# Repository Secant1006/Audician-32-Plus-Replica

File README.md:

# Audician 32 Plus Replica

This is a reverse-engineered sound card based on [Labway A151-A00](https://theretroweb.com/expansioncards/s/labway-corporation-labsound-a00-ide-power-a), which is a Yamaha OPL3-SAx based sound card. The OPL3-SAx is a single solution sound chip which provides Sound Blaster Pro 2.0 and Windows Sound System compatibility, and more importantly, a genuine OPL3 FM synthesizer. It's almost perfect (except ADPCM support) for PC-based retro gaming. Besides outstanding compatibility, this card is also noise-free and has acceptable frequency response.

As of August 2026, no one has published any schematic for this chip yet. This project aims to provide a reverse-engineered schematic and nearly 1:1 clone of the A151-A00 sound card with some modifications:

* Wavetable reverse channel bug is fixed
* Original FCC ID and CE logo are not used
* Silkscreen font is different
* Footprints are replaced with KiCad defaults plus some self-made ones
* Silkscreens for chip model are corrected
* Board is slightly longer and the ISA connector is moved slightly to comply with ISA standard

One configuration of the board is manufactured and validated to work perfectly fine.

# Project Structure

* `bom/`: Interactive BOM
* `eeprom/`: EEPROM dump
* `gerber/`: Gerber files for the PCB
* `jlcpcb/`: JLCPCB production files
* `references/`: Reference documents, including datasheets for chips, ISA standard specification and photos of the original PCB
* Others: KiCad project files

# BOM

| References                                                   | Value                 | LCSC Part Number |
| ------------------------------------------------------------ | --------------------- | ---------------- |
| C4, C7                                                       | 150pF 0805            | C1716            |
| C5, C10                                                      | 220nF 0805            | C5378            |
| C11<sup>[1]</sup>, C12<sup>[1]</sup>, C19<sup>[1]</sup>, C20<sup>[1]</sup>, C44, C45 | 1nF 0805              | C46653           |
| C13, C21, C48, C49, C50, C51                                 | 10nF 0805             | C1710            |
| C14, C33, C37, CB5, CB9, CB15, CB16, CB17                    | 100nF 0805            | C49678           |
| C22, C23, C24, C25, C28, C42, C43, C46                       | 1uF 0805              | C28323           |
| C26, C27                                                     | 470pF 0805            | C1743            |
| C29, CA1                                                     | 100pF 0805            | C1790            |
| C38<sup>[2]</sup>, C39<sup>[2]</sup>                         | 4.7pF 0805            | C1820            |
| C40, C41                                                     | 22pF 0805             | C1804            |
| C47, C52, C54, C55, C58, C59                                 | 47pF 0805             | C14857           |
| CT1, CT2, CT4, CT7, CT8                                      | 100uF D6.3xL7         | C106447          |
| CT3, CT10                                                    | 470uF D8xL11          | C106735          |
| CT5, CT11                                                    | 22uF D5xL7            | C112508          |
| CT6, CT9, CT12, CT13, CT15, CT16                             | 10uF D4xL7            | C5123345         |
| CT14                                                         | 100uF D6.3xL7         | C2826426         |
| R7, R18                                                      | 510Ω 0805             | C17734           |
| R8, R9                                                       | 47kΩ 0805             | C17713           |
| R10, R11, R12, R13                                           | 20kΩ 0805             | C4328            |
| R14, R21, R35                                                | 220kΩ 0805            | C17556           |
| R15, R22, R36                                                | 33kΩ 0805             | C17633           |
| R16, R17, R19, R20                                           | 27kΩ 0805             | C17593           |
| R24, R25                                                     | 7.5kΩ 0805            | C17807           |
| R29<sup>[2]</sup>                                            | 3.9kΩ 0805            | C17614           |
| R30, R32                                                     | 75Ω 0805              | C20638           |
| R31                                                          | 0Ω 0805               | C17477           |
| R33                                                          | 1MΩ 0805              | C17514           |
| R37, R38, R39, R40                                           | 2.2kΩ 0805            | C17520           |
| RA1                                                          | 150Ω                  | C17471           |
| RP1<sup>[3]</sup>                                            | 0Ω 0603x4             | C52175182        |
| RP2                                                          | 2.2kΩ 0603x4          | C52175185        |
| SJ3<sup>[4]</sup>, SJ4<sup>[4]</sup>                         | 0Ω 0805               | C17477           |
| SJ5<sup>[3]</sup>                                            | 0Ω 0805<br>10kΩ 0805  | C17477<br>C17414 |
| D1, D2                                                       | 1N4001 DO-41          | C2456            |
| L2                                                           | Axial D3.5xL4.7       | C192456          |
| Q1                                                           | 78L05 TO-92           | C8608            |
| Q2                                                           | MMBT3904 SOT-23       | C364310          |
| U5                                                           | TEA2025B DIP-16       | C434515          |
| U6<sup>[5]</sup>                                             | OPL3-SAx LQFP-100     |                  |
| U9<sup>[3]</sup>                                             | 93C66 DIP-8           | C434597          |
| U10<sup>[3]</sup>                                            | 74LS138D              | C7736            |
| X2<sup>[2]</sup>                                             | 33.8688MHz HC-49U     |                  |
| X3                                                           | 24.576MHz HC-49U      |                  |
| CN1<sup>[3]</sup>                                            | 2x20pin Dupont 2.54mm | C5224014         |
| CN2                                                          | 2x13pin Dupont 2.54mm | C41430886        |
| J2, J3, J4                                                   | PJ-317                | C381121          |
| J5                                                           | DB-15 Female          | C77835           |
| J10                                                          | 1x4pin Dupont 2.54mm  | C2691448         |
| J11, J13                                                     | 1x4pin JST PH2.0      | C722763          |
| JP1                                                          | 2x3pin Dupont 2.54mm  | C492420          |

Notes:

1. [Low-Pass Filter Mod](https://www.vogons.org/viewtopic.php?p=527947#p527947): This is a mod for this card to make Sound Blaster effects sound more like a real Sound Blaster Pro 2.0. If you want to perform this mod, replace the two SBFLT caps with 6.8nF (LCSC part number C1755). For YMF711/718, the SBFLT caps are C12 and C20. For YMF715/719/741, the SBFLT caps are C11 and C19.
1. C38, C39, R29, X2: If using a 3rd overtone crystal, which most probably is for 33.8688MHz in HC-49U package, then go with the values above. If using a fundamental crystal, then replace C38, C39 and R29 according to the crystal's datasheet. If the card doesn't work correctly then I suggest measuring the crystal output with an oscilloscope.
1. RP1, SJ5, U9, U10, CN1: If you want to use the CD-ROM interface on the sound card, do **NOT** install RP1, install a 10kΩ resistor in SJ5's 1-2 position and a 0Ω in 3-4. Otherwise, install RP1, a 10kΩ resistor in SJ5's **1-3** position and a 0Ω in **2-4**, and do not install U10 and CN1. Then flash the EEPROM (U9) with a programmer. EEPROM images are in the `eeprom/` folder.
1. SJ3, SJ4: Install two 0Ω resistors in 2-3 position.
1. U6: This card supports YMF711 (OPL3-SA2), YMF718 (OPL3-SA2C), YMF715 (OPL3-SA3), YMF719 (OPL3-SA3C) and YMF741 (OPL3-SA3L) in LQFP-100 package. Note that YMF715**F**-S may not work correctly according to some report.

The BOM for the onboard QS1000 wavetable is not listed. Some components, like U7 and some capacitors / resistors, are not present on any variant of this card. I have no idea on what values they are.

As of August 2026, all of the components except the OPL3-SAx chip are still being manufactured. The crystals are not sold by LCSC but they can be sourced through other channels.

# Bracket

The replica should be compatible with the original bracket if the connectors are installed correctly. A model for 3D-printing will be available in the future.

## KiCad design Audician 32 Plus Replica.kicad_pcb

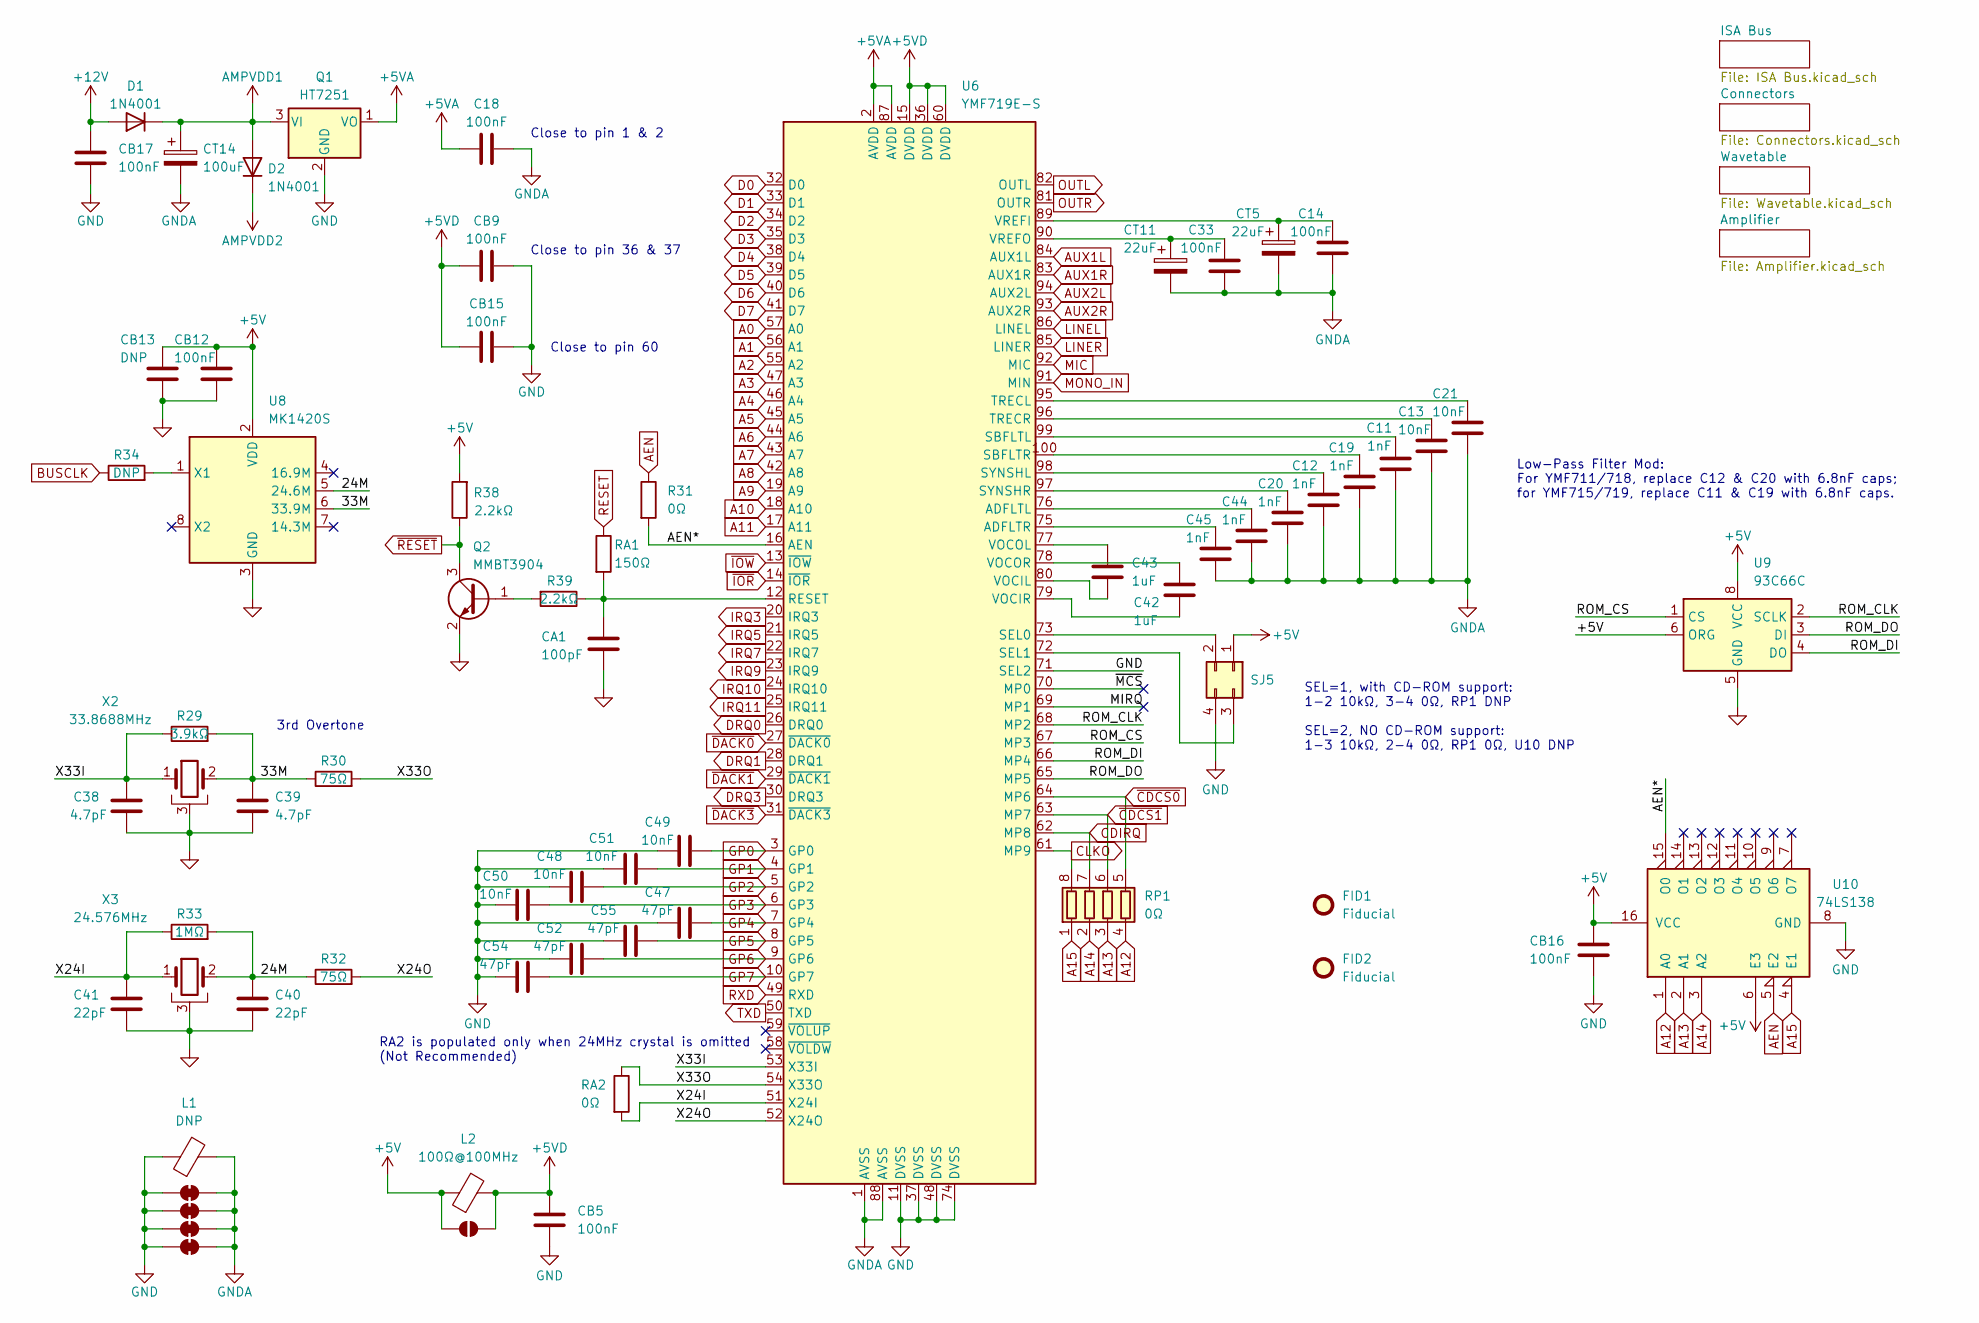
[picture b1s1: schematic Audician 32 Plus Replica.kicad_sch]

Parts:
C11, C19: 1nF; C_0805_2012Metric; LCSC C1755
C12, C20, C44, C45: 1nF; C_0805_2012Metric; LCSC C46653
C13, C21, C48, C49, C50, C51: 10nF; C_0805_2012Metric; LCSC C1710
C14, C33: 100nF; C_0805_2012Metric; LCSC C49678
C18: 100nF; C_0805_2012Metric
C38, C39: 4.7pF; C_0805_2012Metric; LCSC C1820
C40, C41: 22pF; C_0805_2012Metric; LCSC C1804
C42, C43: 1uF; C_0805_2012Metric; LCSC C28323
C47, C52, C54, C55: 47pF; C_0805_2012Metric; LCSC C14857
CA1: 100pF; C_0805_2012Metric; LCSC C1790
CB5, CB9, CB15, CB16, CB17: 100nF; C_0805_2012Metric; LCSC C49678
CB12: 100nF; C_0805_2012Metric
CB13: DNP; C_0805_2012Metric
CT5, CT11: 22uF; CP_Radial_D5.0mm_P2.50mm; LCSC C112508
CT14: 100uF; CP_Radial_D6.3mm_P2.50mm; LCSC C2826426
D1, D2: 1N4001; D_DO-41_SOD81_P10.16mm_Horizontal; LCSC C2456
FID1, FID2: Fiducial; Fiducial_0.75mm_Mask1.5mm
L1: DNP; L_Axial_L7.0mm_D3.3mm_P10.16mm_Horizontal_Fastron_MICC
L2: 100Ω@100MHz; L_Axial_L7.0mm_D3.3mm_P10.16mm_Horizontal_Fastron_MICC; LCSC C192456
Q1: HT7251; TO-92_Inline_Wide; LCSC C5355526
Q2: MMBT3904; SOT-23; LCSC C364310
R29: 3.9kΩ; R_0805_2012Metric; LCSC C17614
R30, R32: 75Ω; R_0805_2012Metric; LCSC C20638
R31: 0Ω; R_0805_2012Metric; LCSC C17477
R33: 1MΩ; R_0805_2012Metric; LCSC C17514
R34: DNP; R_0805_2012Metric
R38, R39: 2.2kΩ; R_0805_2012Metric; LCSC C17520
RA1: 150Ω; R_0805_2012Metric; LCSC C17471
RA2: 0Ω; R_0805_2012Metric
RP1: 0Ω; R_Array_Convex_4x0603; LCSC C52175182
SJ5: Conn_02x02; SolderJumper_02x02_0805; LCSC C17414
SJL1, SJL4, SJL5, SJL6: SolderJumper_2_Bridged; SolderJumper-2_P1.3mm_Bridged_RoundedPad1.0x1.5mm
SJL2: SolderJumper_2_Open; SolderJumper-2_P1.3mm_Open_RoundedPad1.0x1.5mm
U6: YMF719E-S; LQFP-100_14x14mm_P0.5mm
U8: MK1420S; SOIC-8_3.9x4.9mm_P1.27mm
U9: 93C66C; DIP-8_W7.62mm; LCSC C434597
U10: 74LS138; SOIC-16_3.9x9.9mm_P1.27mm
X2: 33.8688MHz; Crystal_HC49-U_Horizontal_1EP_style2
X3: 24.576MHz; Crystal_HC49-U_Horizontal_1EP_style2

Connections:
+5V: CB12.1, CB13.1, CB16.1, L2.1, R38.2, SJ5.1, SJL2.1 (A), U8.2 (VDD), U9.6 (ORG), U9.8 (VCC), U10.6 (E3), U10.16 (VCC); also elsewhere on the board
+5VA: C18.1, Q1.1 (VO), U6.2 (AVDD), U6.87 (AVDD); also elsewhere on the board
+5VD: CB5.2, CB9.1, CB15.1, L2.2, SJL2.2 (B), U6.15 (DVDD), U6.36 (DVDD), U6.60 (DVDD)
+12V: CB17.1, D1.2 (A); also elsewhere on the board
/24M: C40.1, R32.1, R33.2, U8.5 (24.6M), X3.2
/33M: C39.1, R29.2, R30.1, U8.6 (33.9M), X2.2
/AEN*: R31.2, U6.16 (AEN), U10.15 (O0)
/MIRQ: U6.69 (MP1)
/ROM_CLK: U6.68 (MP2), U9.2 (SCLK)
/ROM_CS: U6.67 (MP3), U9.1 (CS)
/ROM_DI: U6.66 (MP4), U9.4 (DO)
/ROM_DO: U6.65 (MP5), U9.3 (DI)
/X24I: C41.1, R33.1, RA2.2, U6.51 (X24I), X3.1
/X24O: R32.2, U6.52 (X24O)
/X33I: C38.1, R29.1, U6.53 (X33I), X2.1
/X33O: R30.2, RA2.1, U6.54 (X33O)
/~MCS: U6.70 (MP0)
A0: U6.57 (A0); also elsewhere on the board
A1: U6.56 (A1); also elsewhere on the board
A2: U6.55 (A2); also elsewhere on the board
A3: U6.47 (A3); also elsewhere on the board
A4: U6.46 (A4); also elsewhere on the board
A5: U6.45 (A5); also elsewhere on the board
A6: U6.44 (A6); also elsewhere on the board
A7: U6.43 (A7); also elsewhere on the board
A8: U6.42 (A8); also elsewhere on the board
A9: U6.19 (A9); also elsewhere on the board
A10: U6.18 (A10); also elsewhere on the board
A11: U6.17 (A11); also elsewhere on the board
A12: RP1.4 (R4.1), U10.1 (A0); also elsewhere on the board
A13: RP1.3 (R3.1), U10.2 (A1); also elsewhere on the board
A14: RP1.2 (R2.1), U10.3 (A2); also elsewhere on the board
A15: RP1.1 (R1.1), U10.4 (E1); also elsewhere on the board
AEN: R31.1, U10.5 (E2); also elsewhere on the board
AMPVDD1: CT14.1, D1.1 (K), D2.2 (A), Q1.3 (VI); also elsewhere on the board
AMPVDD2: D2.1 (K); also elsewhere on the board
AUX1L: U6.84 (AUX1L); also elsewhere on the board
AUX1R: U6.83 (AUX1R); also elsewhere on the board
AUX2L: U6.94 (AUX2L); also elsewhere on the board
AUX2R: U6.93 (AUX2R); also elsewhere on the board
BUSCLK: R34.1; also elsewhere on the board
CDIRQ: RP1.7 (R2.2), U6.62 (MP8); also elsewhere on the board
CLKO: RP1.8 (R1.2), U6.61 (MP9)
D0: U6.32 (D0); also elsewhere on the board
D1: U6.33 (D1); also elsewhere on the board
D2: U6.34 (D2); also elsewhere on the board
D3: U6.35 (D3); also elsewhere on the board
D4: U6.38 (D4); also elsewhere on the board
D5: U6.39 (D5); also elsewhere on the board
D6: U6.40 (D6); also elsewhere on the board
D7: U6.41 (D7); also elsewhere on the board
DRQ0: U6.26 (DRQ0); also elsewhere on the board
DRQ1: U6.28 (DRQ1); also elsewhere on the board
DRQ3: U6.30 (DRQ3); also elsewhere on the board
GND: C38.2, C39.2, C40.2, C41.2, C47.1, C48.1, C49.1, C50.1, C51.1, C52.1, C54.1, C55.1, CA1.2, CB5.1, CB9.2, CB12.2, CB13.2, CB15.2, CB16.2, CB17.2, L1.1, Q1.2 (GND), Q2.2 (E), SJ5.4, SJL1.1 (A), SJL4.1 (A), SJL5.1 (A), SJL6.1 (A), U6.11 (DVSS), U6.37 (DVSS), U6.48 (DVSS), U6.71 (SEL2), U6.74 (DVSS), U8.3 (GND), U9.5 (GND), U10.8 (GND), X2.3, X3.3; also elsewhere on the board
GNDA: C11.1, C12.1, C13.1, C14.2, C18.2, C19.1, C20.1, C21.1, C33.1, C44.1, C45.1, CT5.2, CT11.2, CT14.2, L1.2, SJL1.2 (B), SJL4.2 (B), SJL5.2 (B), SJL6.2 (B), U6.1 (AVSS), U6.88 (AVSS); also elsewhere on the board
GP0: C49.2, U6.3 (GP0); also elsewhere on the board
GP1: C51.2, U6.4 (GP1); also elsewhere on the board
GP2: C48.2, U6.5 (GP2); also elsewhere on the board
GP3: C50.2, U6.6 (GP3); also elsewhere on the board
GP4: C47.2, U6.7 (GP4); also elsewhere on the board
GP5: C55.2, U6.8 (GP5); also elsewhere on the board
GP6: C52.2, U6.9 (GP6); also elsewhere on the board
GP7: C54.2, U6.10 (GP7); also elsewhere on the board
IRQ3: U6.20 (IRQ3); also elsewhere on the board
IRQ5: U6.21 (IRQ5); also elsewhere on the board
IRQ7: U6.22 (IRQ7); also elsewhere on the board
IRQ9: U6.23 (IRQ9); also elsewhere on the board
IRQ10: U6.24 (IRQ10); also elsewhere on the board
IRQ11: U6.25 (IRQ11); also elsewhere on the board
LINEL: U6.86 (LINEL); also elsewhere on the board
LINER: U6.85 (LINER); also elsewhere on the board
MIC: U6.92 (MIC); also elsewhere on the board
MONO_IN: U6.91 (MIN); also elsewhere on the board
unnamed: Q2.1 (B), R39.2
unnamed: SJ5.2, U6.73 (SEL0)
unnamed: SJ5.3, U6.72 (SEL1)
unnamed: C44.2, U6.76 (ADFLTL)
unnamed: C45.2, U6.75 (ADFLTR)
unnamed: CA1.1, R39.1, RA1.2, U6.12 (RESET)
unnamed: C11.2, U6.99 (SBFLTL)
unnamed: C19.2, U6.100 (SBFLTR)
unnamed: C12.2, U6.98 (SYNSHL)
unnamed: C20.2, U6.97 (SYNSHR)
unnamed: C21.2, U6.95 (TRECL)
unnamed: C13.2, U6.96 (TRECR)
unnamed: C43.2, U6.80 (VOCIL)
unnamed: C42.2, U6.79 (VOCIR)
unnamed: C43.1, U6.77 (VOCOL)
unnamed: C42.1, U6.78 (VOCOR)
unnamed: C14.1, CT5.1, U6.89 (VREFI)
unnamed: C33.2, CT11.1, U6.90 (VREFO)
unnamed: R34.2, U8.1 (X1)
OUTL: U6.82 (OUTL); also elsewhere on the board
OUTR: U6.81 (OUTR); also elsewhere on the board
RESET: RA1.1; also elsewhere on the board
RXD: U6.49 (RXD); also elsewhere on the board
TXD: U6.50 (TXD); also elsewhere on the board
~CDCS0: RP1.5 (R4.2), U6.64 (MP6); also elsewhere on the board
~CDCS1: RP1.6 (R3.2), U6.63 (MP7); also elsewhere on the board
~DACK0: U6.27 (~DACK0); also elsewhere on the board
~DACK1: U6.29 (~DACK1); also elsewhere on the board
~DACK3: U6.31 (~DACK3); also elsewhere on the board
~IOR: U6.14 (~IOR); also elsewhere on the board
~IOW: U6.13 (~IOW); also elsewhere on the board
~RESET: Q2.3 (C), R38.1; also elsewhere on the board

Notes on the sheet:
SEL=1, with CD-ROM support: 1-2 10kΩ, 3-4 0Ω, RP1 DNP SEL=2, NO CD-ROM support: 1-3 10kΩ, 2-4 0Ω, RP1 0Ω, U10 DNP
Close to pin 1 & 2
Low-Pass Filter Mod: For YMF711/718, replace C12 & C20 with 6.8nF caps; for YMF715/719, replace C11 & C19 with 6.8nF caps.
Close to pin 36 & 37
3rd Overtone
Close to pin 60
RA2 is populated only when 24MHz crystal is omitted (Not Recommended)

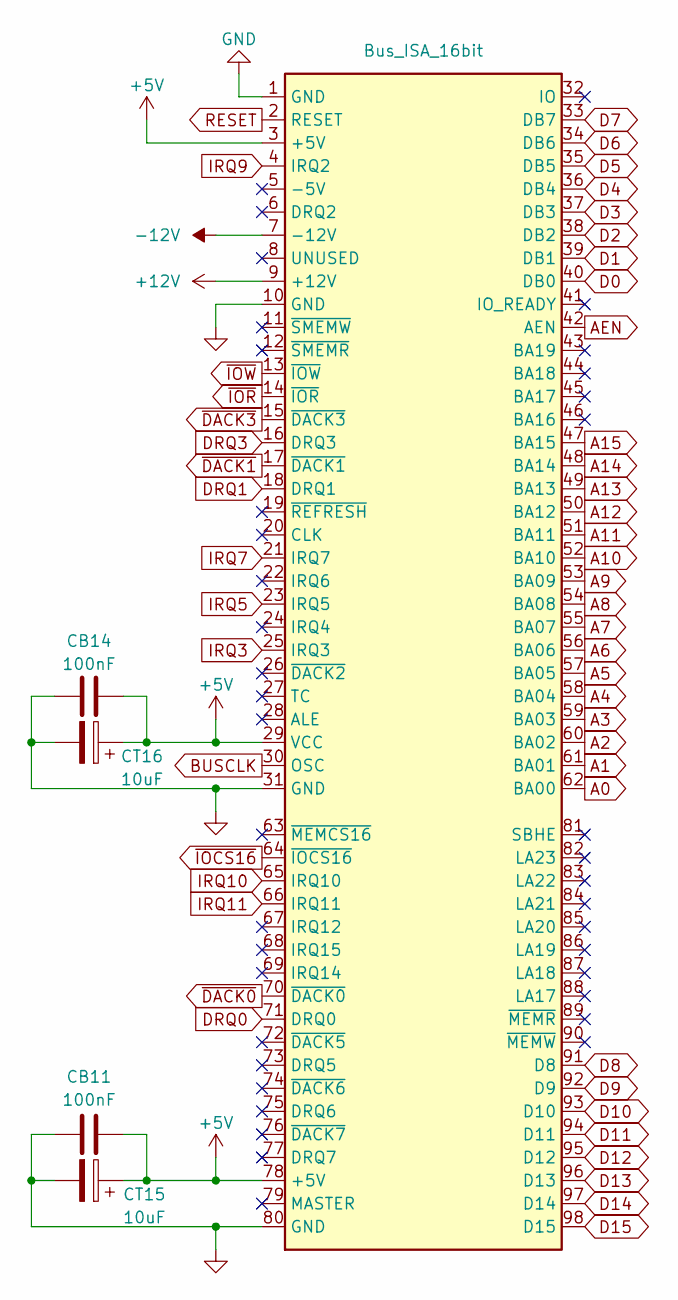
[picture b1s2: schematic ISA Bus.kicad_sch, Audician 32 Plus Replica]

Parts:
CB11, CB14: 100nF; C_0805_2012Metric
CT15, CT16: 10uF; CP_Radial_D5.0mm_P2.50mm; LCSC C5123345
J1: Bus_ISA_16bit; BUS_AT

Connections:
+5V: CB11.2, CB14.2, CT15.1, CT16.1, J1.3 (+5V), J1.29 (VCC), J1.78 (+5V); also elsewhere on the board
+12V: J1.9 (+12V); also elsewhere on the board
-12V: J1.7 (-12V); also elsewhere on the board
A0: J1.62 (BA00); also elsewhere on the board
A1: J1.61 (BA01); also elsewhere on the board
A2: J1.60 (BA02); also elsewhere on the board
A3: J1.59 (BA03); also elsewhere on the board
A4: J1.58 (BA04); also elsewhere on the board
A5: J1.57 (BA05); also elsewhere on the board
A6: J1.56 (BA06); also elsewhere on the board
A7: J1.55 (BA07); also elsewhere on the board
A8: J1.54 (BA08); also elsewhere on the board
A9: J1.53 (BA09); also elsewhere on the board
A10: J1.52 (BA10); also elsewhere on the board
A11: J1.51 (BA11); also elsewhere on the board
A12: J1.50 (BA12); also elsewhere on the board
A13: J1.49 (BA13); also elsewhere on the board
A14: J1.48 (BA14); also elsewhere on the board
A15: J1.47 (BA15); also elsewhere on the board
AEN: J1.42 (AEN); also elsewhere on the board
BUSCLK: J1.30 (OSC); also elsewhere on the board
D0: J1.40 (DB0); also elsewhere on the board
D1: J1.39 (DB1); also elsewhere on the board
D2: J1.38 (DB2); also elsewhere on the board
D3: J1.37 (DB3); also elsewhere on the board
D4: J1.36 (DB4); also elsewhere on the board
D5: J1.35 (DB5); also elsewhere on the board
D6: J1.34 (DB6); also elsewhere on the board
D7: J1.33 (DB7); also elsewhere on the board
D8: J1.91 (D8); also elsewhere on the board
D9: J1.92 (D9); also elsewhere on the board
D10: J1.93 (D10); also elsewhere on the board
D11: J1.94 (D11); also elsewhere on the board
D12: J1.95 (D12); also elsewhere on the board
D13: J1.96 (D13); also elsewhere on the board
D14: J1.97 (D14); also elsewhere on the board
D15: J1.98 (D15); also elsewhere on the board
DRQ0: J1.71 (DRQ0); also elsewhere on the board
DRQ1: J1.18 (DRQ1); also elsewhere on the board
DRQ3: J1.16 (DRQ3); also elsewhere on the board
GND: CB11.1, CB14.1, CT15.2, CT16.2, J1.1 (GND), J1.10 (GND), J1.31 (GND), J1.80 (GND); also elsewhere on the board
IRQ3: J1.25 (IRQ3); also elsewhere on the board
IRQ5: J1.23 (IRQ5); also elsewhere on the board
IRQ7: J1.21 (IRQ7); also elsewhere on the board
IRQ9: J1.4 (IRQ2); also elsewhere on the board
IRQ10: J1.65 (IRQ10); also elsewhere on the board
IRQ11: J1.66 (IRQ11); also elsewhere on the board
RESET: J1.2 (RESET); also elsewhere on the board
~DACK0: J1.70 (~DACK0); also elsewhere on the board
~DACK1: J1.17 (~DACK1); also elsewhere on the board
~DACK3: J1.15 (~DACK3); also elsewhere on the board
~IOCS16: J1.64 (~IOCS16); also elsewhere on the board
~IOR: J1.14 (~IOR); also elsewhere on the board
~IOW: J1.13 (~IOW); also elsewhere on the board

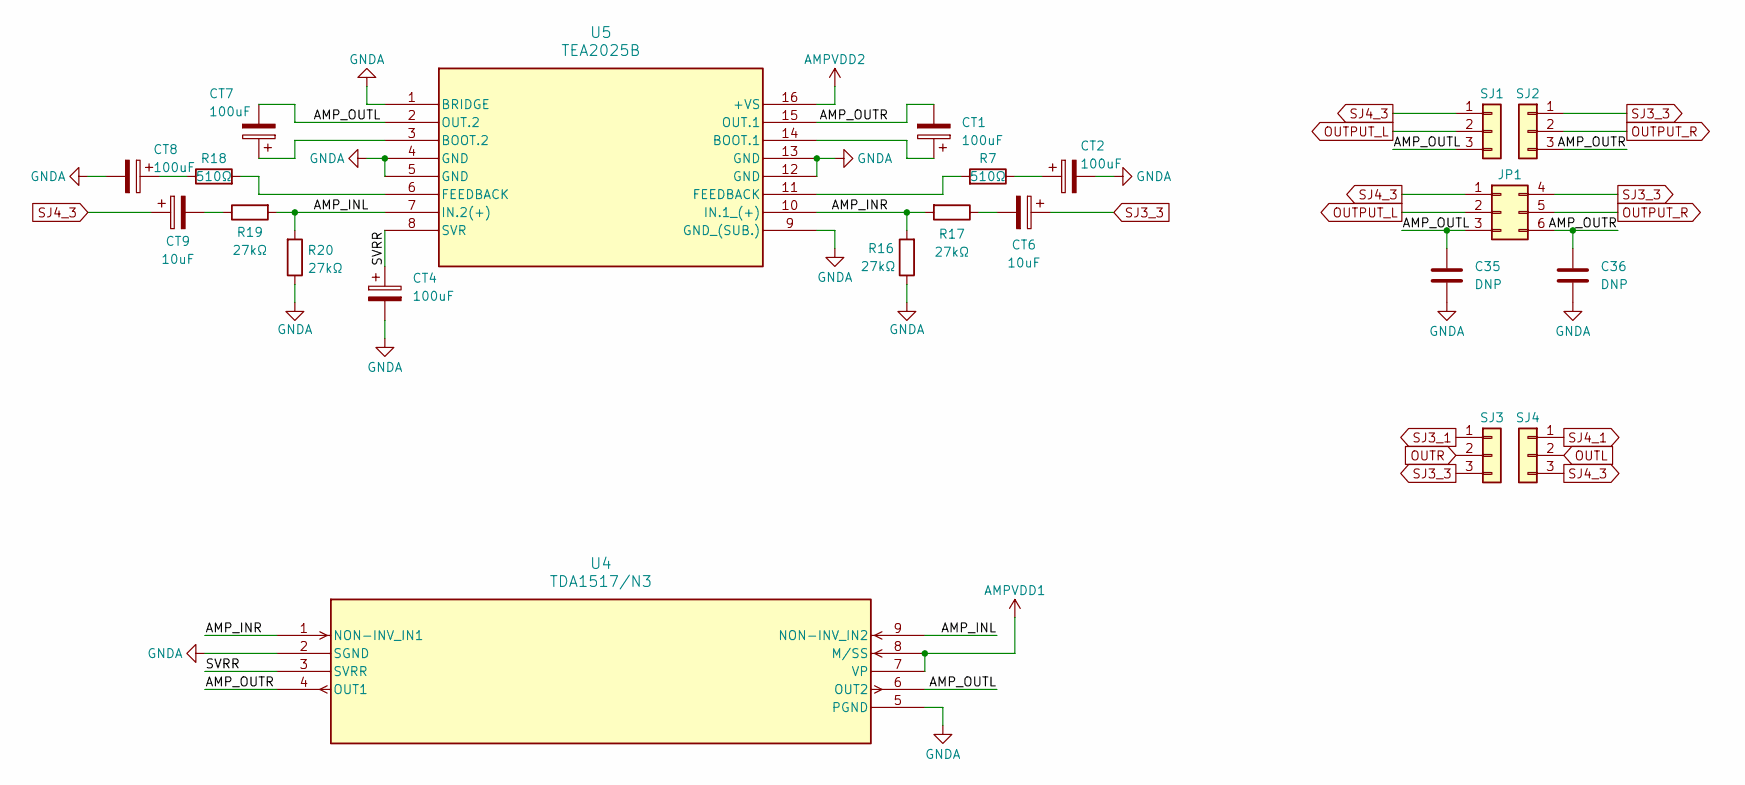
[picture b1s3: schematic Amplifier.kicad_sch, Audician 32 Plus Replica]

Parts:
C35, C36: DNP; C_0805_2012Metric
CT1, CT2, CT4, CT7, CT8: 100uF; CP_Radial_D6.3mm_P2.50mm; LCSC C106447
CT6, CT9: 10uF; CP_Radial_D5.0mm_P2.50mm; LCSC C5123345
JP1: Conn_02x03_Top_Bottom; PinHeader_2x03_P2.54mm_Vertical; LCSC C492420
R7, R18: 510Ω; R_0805_2012Metric; LCSC C17734
R16, R17, R19, R20: 27kΩ; R_0805_2012Metric; LCSC C17593
SJ1, SJ2: Conn_01x03; SolderJumper_01x03_0805
SJ3, SJ4: Conn_01x03; SolderJumper_01x03_0805; LCSC C17477
U4: TDA1517/N3; SIP-9_21.54x3mm_P2.54mm
U5: TEA2025B; PowerDIP-16_W7.62mm; LCSC C434515

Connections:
/Amplifier/AMP_INL: R19.2, R20.2, U4.9 (NON-INV_IN2), U5.7 (IN.2(+))
/Amplifier/AMP_INR: R16.2, R17.2, U4.1 (NON-INV_IN1), U5.10 (IN.1_(+))
/Amplifier/AMP_OUTL: C35.1, CT7.2, JP1.3, SJ1.3, U4.6 (OUT2), U5.2 (OUT.2)
/Amplifier/AMP_OUTR: C36.1, CT1.2, JP1.6, SJ2.3, U4.4 (OUT1), U5.15 (OUT.1)
/Amplifier/SVRR: CT4.1, U4.3 (SVRR), U5.8 (SVR)
AMPVDD1: U4.7 (VP), U4.8 (M/SS); also elsewhere on the board
AMPVDD2: U5.16 (+VS); also elsewhere on the board
GNDA: C35.2, C36.2, CT2.2, CT4.2, CT8.2, R16.1, R20.1, U4.2 (SGND), U4.5 (PGND), U5.1 (BRIDGE), U5.4 (GND), U5.5 (GND), U5.9 (GND_(SUB.)), U5.12 (GND), U5.13 (GND); also elsewhere on the board
unnamed: CT2.1, R7.1
unnamed: CT6.2, R17.1
unnamed: CT8.1, R18.1
unnamed: CT9.2, R19.1
unnamed: R7.2, U5.11 (FEEDBACK)
unnamed: R18.2, U5.6 (FEEDBACK)
unnamed: CT1.1, U5.14 (BOOT.1)
unnamed: CT7.1, U5.3 (BOOT.2)
OUTL: SJ4.2; also elsewhere on the board
OUTPUT_L: JP1.2, SJ1.2; also elsewhere on the board
OUTPUT_R: JP1.5, SJ2.2; also elsewhere on the board
OUTR: SJ3.2; also elsewhere on the board
SJ3_1: SJ3.1; also elsewhere on the board
SJ3_3: CT6.1, JP1.4, SJ2.1, SJ3.3; also elsewhere on the board
SJ4_1: SJ4.1; also elsewhere on the board
SJ4_3: CT9.1, JP1.1, SJ1.1, SJ4.3; also elsewhere on the board

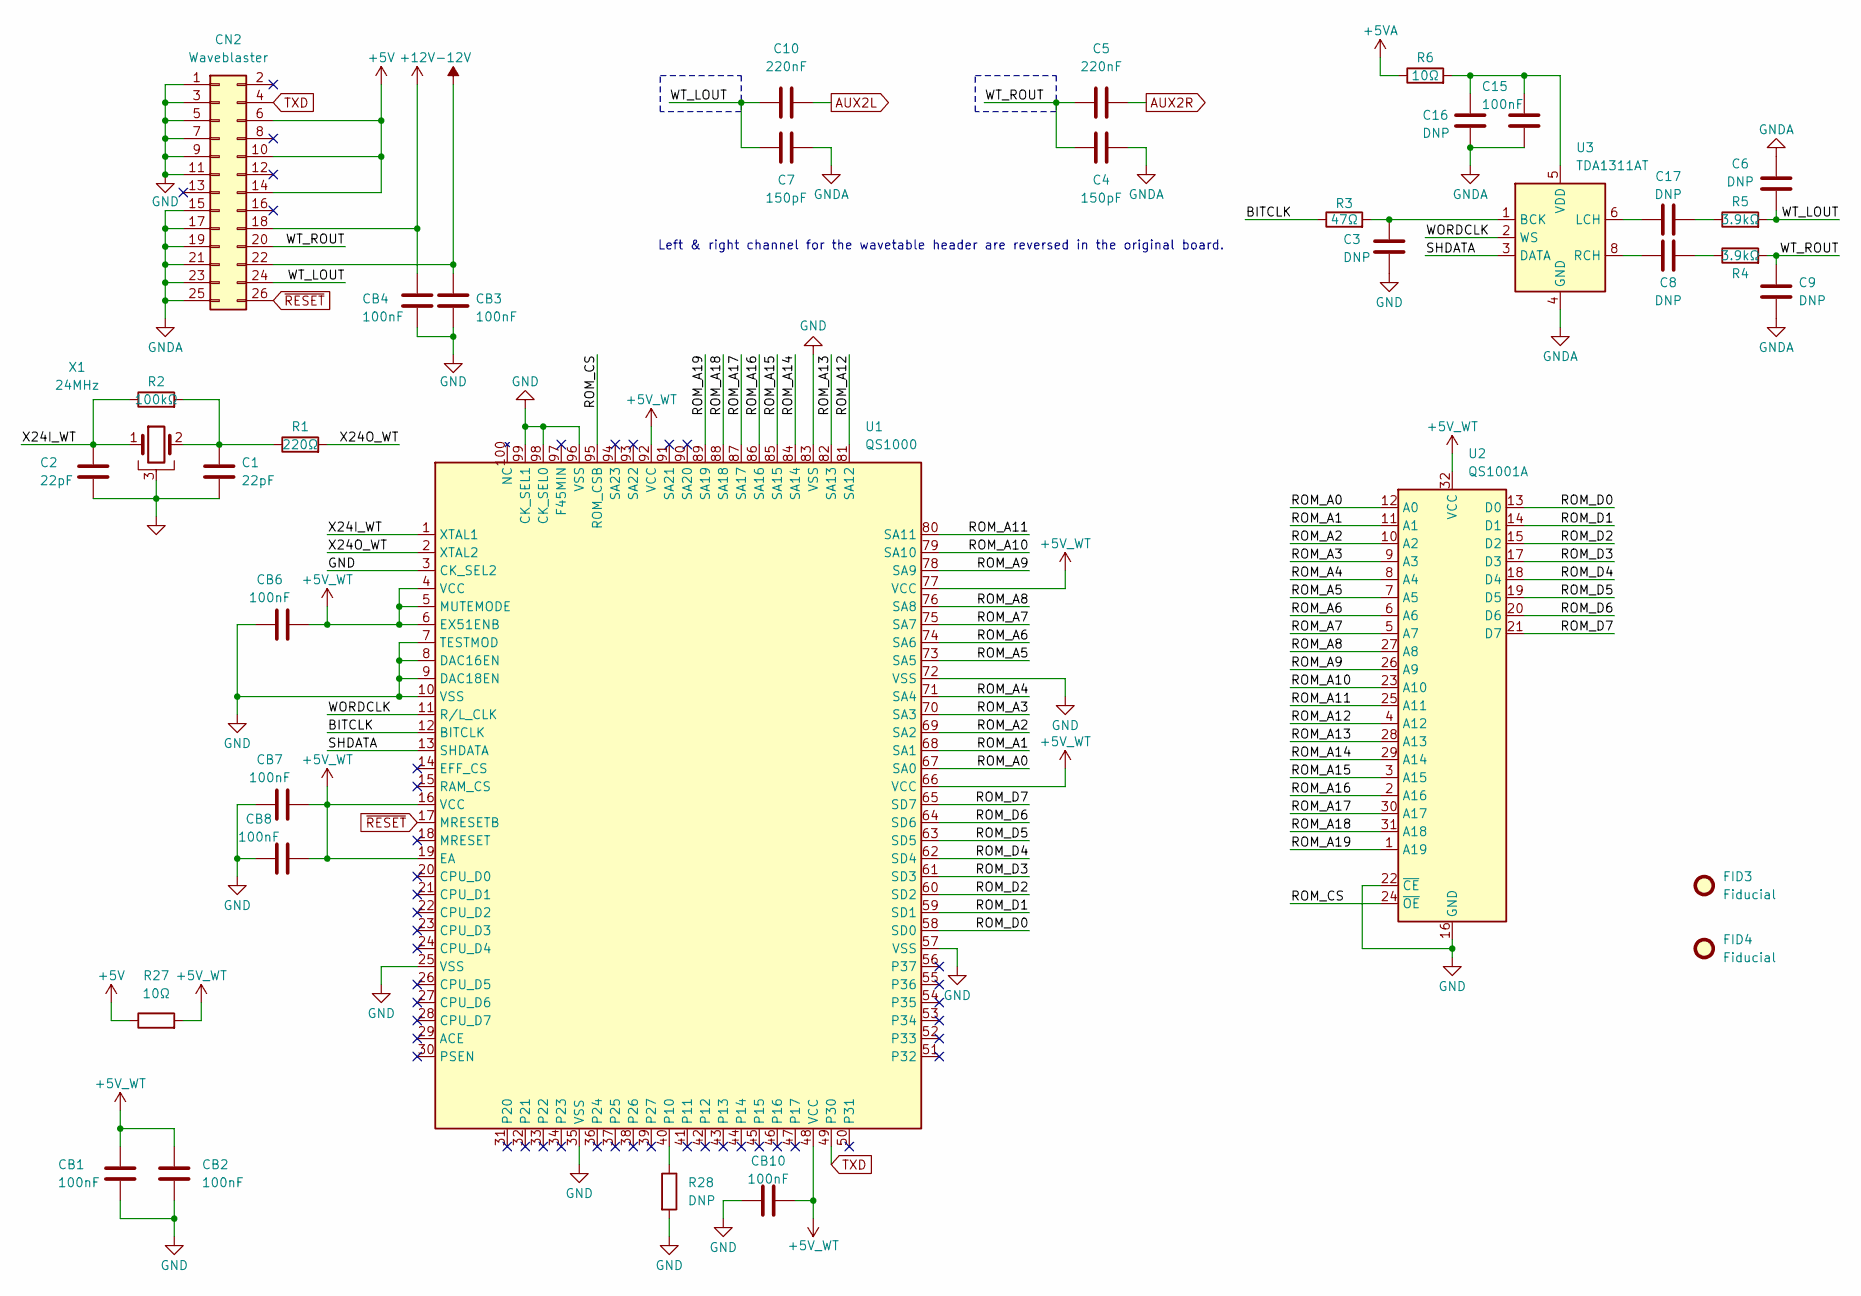
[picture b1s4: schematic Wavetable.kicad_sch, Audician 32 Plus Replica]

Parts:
C1, C2: 22pF; C_0805_2012Metric
C3, C6, C8, C9, C16, C17: DNP; C_0805_2012Metric
C4, C7: 150pF; C_0805_2012Metric; LCSC C1716
C5, C10: 220nF; C_0805_2012Metric; LCSC C5378
C15: 100nF; C_0805_2012Metric
CB1, CB2, CB3, CB4, CB6, CB7, CB8, CB10: 100nF; C_0805_2012Metric
CN2: Waveblaster; PinHeader_2x13_P2.54mm_Vertical; LCSC C41430886
FID3, FID4: Fiducial; Fiducial_0.75mm_Mask1.5mm
R1: 220Ω; R_0805_2012Metric
R2: 100kΩ; R_0805_2012Metric
R3: 47Ω; R_0805_2012Metric
R4, R5: 3.9kΩ; R_0805_2012Metric
R6, R27: 10Ω; R_0805_2012Metric
R28: DNP; R_0805_2012Metric
U1: QS1000; PQFP-100_14x20mm_P0.65mm
U2: QS1001A; SOP-32_11.305x20.495mm_P1.27mm
U3: TDA1311AT; SOIC-8_3.9x4.9mm_P1.27mm
X1: 24MHz; Crystal_HC49-U_Horizontal_1EP_style2

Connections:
+5V: CN2.6, CN2.10, CN2.14, R27.1; also elsewhere on the board
+5VA: R6.1; also elsewhere on the board
+5V_WT: CB1.1, CB2.1, CB6.2, CB7.2, CB8.2, CB10.2, R27.2, U1.4 (VCC), U1.5 (MUTEMODE), U1.6 (EX51ENB), U1.16 (VCC), U1.19 (EA), U1.48 (VCC), U1.66 (VCC), U1.77 (VCC), U1.92 (VCC), U2.32 (VCC)
+12V: CB4.1, CN2.18; also elsewhere on the board
-12V: CB3.1, CN2.22; also elsewhere on the board
/Wavetable/BITCLK: R3.1, U1.12 (BITCLK)
/Wavetable/ROM_A0: U1.67 (SA0), U2.12 (A0)
/Wavetable/ROM_A1: U1.68 (SA1), U2.11 (A1)
/Wavetable/ROM_A2: U1.69 (SA2), U2.10 (A2)
/Wavetable/ROM_A3: U1.70 (SA3), U2.9 (A3)
/Wavetable/ROM_A4: U1.71 (SA4), U2.8 (A4)
/Wavetable/ROM_A5: U1.73 (SA5), U2.7 (A5)
/Wavetable/ROM_A6: U1.74 (SA6), U2.6 (A6)
/Wavetable/ROM_A7: U1.75 (SA7), U2.5 (A7)
/Wavetable/ROM_A8: U1.76 (SA8), U2.27 (A8)
/Wavetable/ROM_A9: U1.78 (SA9), U2.26 (A9)
/Wavetable/ROM_A10: U1.79 (SA10), U2.23 (A10)
/Wavetable/ROM_A11: U1.80 (SA11), U2.25 (A11)
/Wavetable/ROM_A12: U1.81 (SA12), U2.4 (A12)
/Wavetable/ROM_A13: U1.82 (SA13), U2.28 (A13)
/Wavetable/ROM_A14: U1.84 (SA14), U2.29 (A14)
/Wavetable/ROM_A15: U1.85 (SA15), U2.3 (A15)
/Wavetable/ROM_A16: U1.86 (SA16), U2.2 (A16)
/Wavetable/ROM_A17: U1.87 (SA17), U2.30 (A17)
/Wavetable/ROM_A18: U1.88 (SA18), U2.31 (A18)
/Wavetable/ROM_A19: U1.89 (SA19), U2.1 (A19)
/Wavetable/ROM_CS: U1.95 (ROM_CSB), U2.24 (~OE)
/Wavetable/ROM_D0: U1.58 (SD0), U2.13 (D0)
/Wavetable/ROM_D1: U1.59 (SD1), U2.14 (D1)
/Wavetable/ROM_D2: U1.60 (SD2), U2.15 (D2)
/Wavetable/ROM_D3: U1.61 (SD3), U2.17 (D3)
/Wavetable/ROM_D4: U1.62 (SD4), U2.18 (D4)
/Wavetable/ROM_D5: U1.63 (SD5), U2.19 (D5)
/Wavetable/ROM_D6: U1.64 (SD6), U2.20 (D6)
/Wavetable/ROM_D7: U1.65 (SD7), U2.21 (D7)
/Wavetable/SHDATA: U1.13 (SHDATA), U3.3 (DATA)
/Wavetable/WORDCLK: U1.11 (R/L_CLK), U3.2 (WS)
/Wavetable/WT_LOUT: C6.1, C7.1, C10.1, CN2.24, R5.2
/Wavetable/WT_ROUT: C4.1, C5.1, C9.1, CN2.20, R4.2
/Wavetable/X24I_WT: C2.1, R2.1, U1.1 (XTAL1), X1.1
/Wavetable/X24O_WT: R1.2, U1.2 (XTAL2)
AUX2L: C10.2; also elsewhere on the board
AUX2R: C5.2; also elsewhere on the board
GND: C1.2, C2.2, C3.2, CB1.2, CB2.2, CB3.2, CB4.2, CB6.1, CB7.1, CB8.1, CB10.1, CN2.1, CN2.3, CN2.5, CN2.7, CN2.9, CN2.11, R28.2, U1.3 (CK_SEL2), U1.7 (TESTMOD), U1.8 (DAC16EN), U1.9 (DAC18EN), U1.10 (VSS), U1.25 (VSS), U1.35 (VSS), U1.57 (VSS), U1.72 (VSS), U1.83 (VSS), U1.96 (VSS), U1.98 (CK_SEL0), U1.99 (CK_SEL1), U2.16 (GND), U2.22 (~CE), X1.3; also elsewhere on the board
GNDA: C4.2, C6.2, C7.2, C9.2, C15.2, C16.2, CN2.15, CN2.17, CN2.19, CN2.21, CN2.23, CN2.25, U3.4 (GND); also elsewhere on the board
unnamed: C1.1, R1.1, R2.2, X1.2
unnamed: C8.1, R4.1
unnamed: C17.2, R5.1
unnamed: R28.1, U1.40 (P10)
unnamed: C3.1, R3.2, U3.1 (BCK)
unnamed: C17.1, U3.6 (LCH)
unnamed: C8.2, U3.8 (RCH)
unnamed: C15.1, C16.1, R6.2, U3.5 (VDD)
TXD: CN2.4, U1.49 (P30); also elsewhere on the board
~RESET: CN2.26, U1.17 (MRESETB); also elsewhere on the board

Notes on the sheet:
Left & right channel for the wavetable header are reversed in the original board.
